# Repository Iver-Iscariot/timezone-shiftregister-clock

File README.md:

# Timezone clock
Expandable, dynamic system for showing the time in different timezones.

Originally designed for use in Omega Verksted, as several members exchanged to different timezones.

The modules are chained together with one MCU at the end. The timezone for each module is set using the dip switch, and read to the MCU by shift registers. The corresponding numbers for 7-seg displays are then sent out on further registers. The dip-switch also instructs weather its the last in the chain, and if its supposed to show the minutes or the hours of the zone. The clock is design to be installed in two rows, one for hours and one for minutes

## Time zone DIP switch table
coming

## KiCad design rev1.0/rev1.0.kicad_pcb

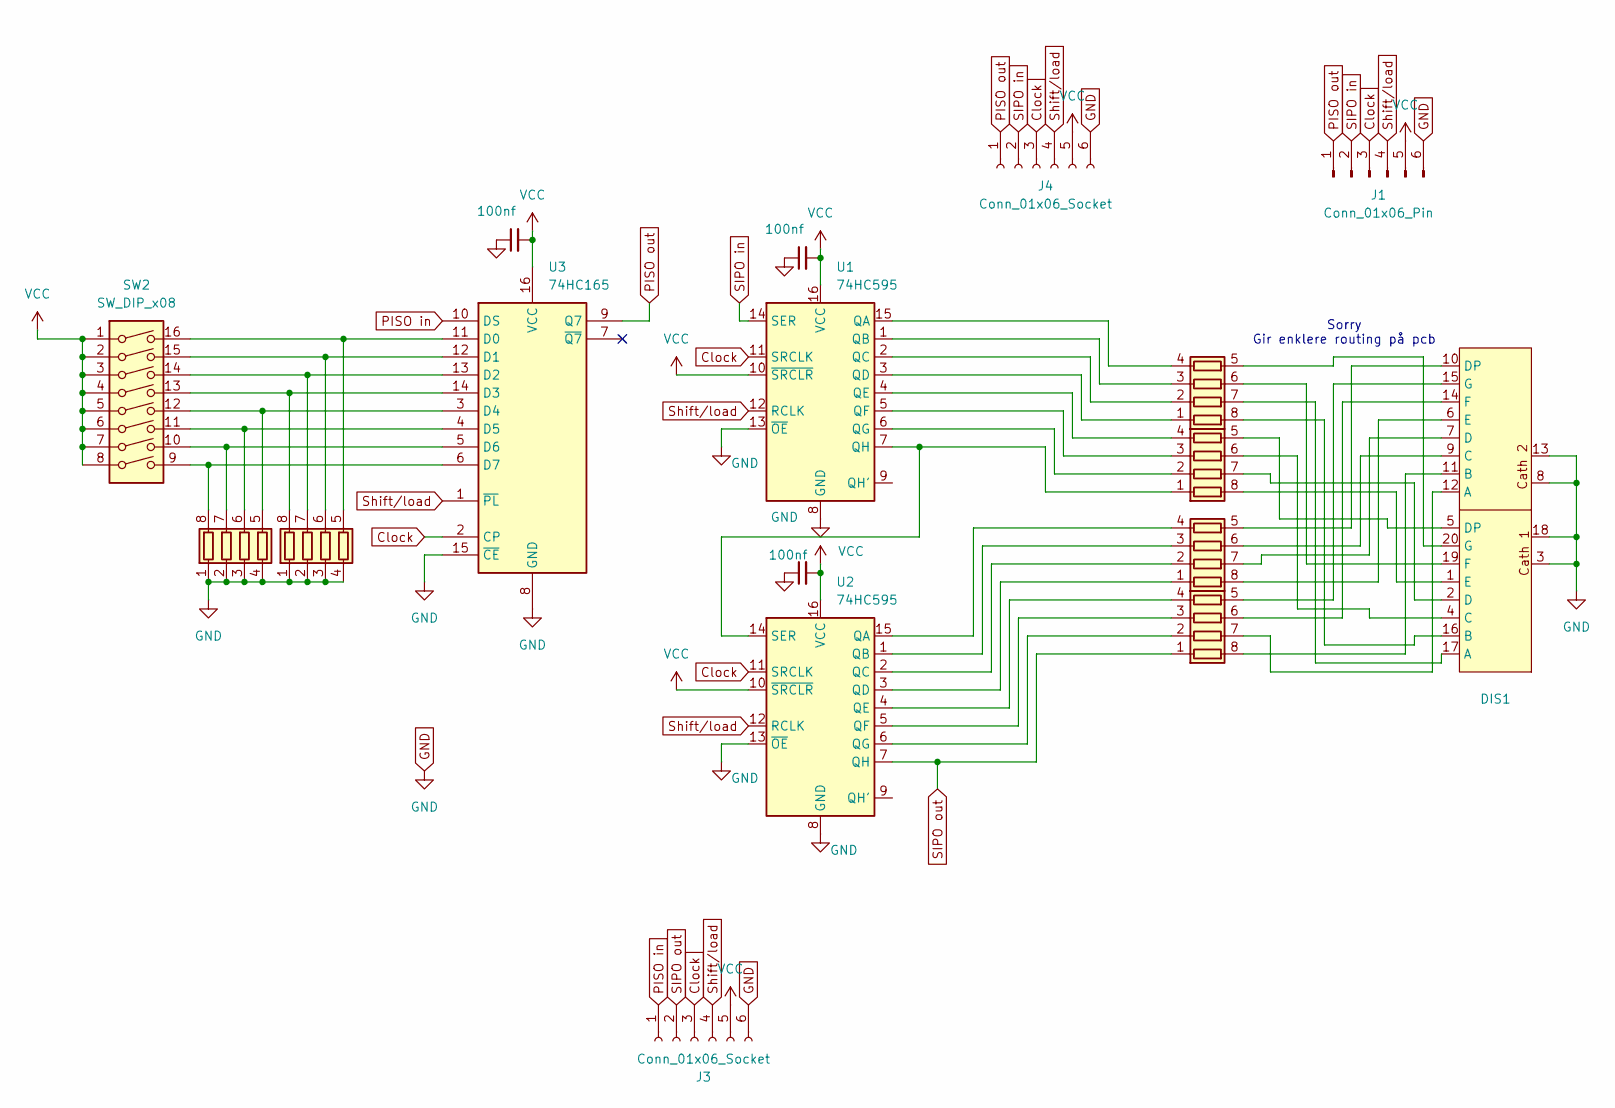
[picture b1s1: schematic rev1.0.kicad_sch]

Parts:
C1, C2, C3: 100nf; C_0603_1608Metric
DIS1: double digit 7 seg
J1: Conn_01x06_Pin; PinHeader_1x06_P2.54mm_Horizontal
J3, J4: Conn_01x06_Socket; flatcable conn 6
RN1, RN2, RN3, RN4, RN5, RN6: R_Pack04; R_Array_Concave_4x0603
SW2: SW_DIP_x08; SOIC-16_3.9x9.9mm_P1.27mm
U1, U2: 74HC595; SOIC-16_3.9x9.9mm_P1.27mm
U3: 74HC165; SOIC-16_3.9x9.9mm_P1.27mm

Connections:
Clock: J1.3, J3.3, J4.3, U1.11 (SRCLK), U2.11 (SRCLK), U3.2 (CP)
GND: C1.1, C2.1, C3.1, DIS1.3, DIS1.8, DIS1.13, DIS1.18, J1.6, J3.6, J4.6, RN1.1 (R1.1), RN1.2 (R2.1), RN1.3 (R3.1), RN1.4 (R4.1), RN2.1 (R1.1), RN2.2 (R2.1), RN2.3 (R3.1), RN2.4 (R4.1), U1.8 (GND), U1.13 (~OE), U2.8 (GND), U2.13 (~OE), U3.8 (GND), U3.15 (~CE)
unnamed: RN1.8 (R1.2), SW2.9, U3.6 (D7)
unnamed: RN1.7 (R2.2), SW2.10, U3.5 (D6)
unnamed: RN1.6 (R3.2), SW2.11, U3.4 (D5)
unnamed: RN1.5 (R4.2), SW2.12, U3.3 (D4)
unnamed: RN2.8 (R1.2), SW2.13, U3.14 (D3)
unnamed: RN2.7 (R2.2), SW2.14, U3.13 (D2)
unnamed: RN2.6 (R3.2), SW2.15, U3.12 (D1)
unnamed: RN2.5 (R4.2), SW2.16, U3.11 (D0)
unnamed: RN3.1 (R1.1), U1.3 (QD)
unnamed: DIS1.16 (B), RN3.8 (R1.2)
unnamed: RN3.2 (R2.1), U1.2 (QC)
unnamed: DIS1.17 (A), RN3.7 (R2.2)
unnamed: RN3.3 (R3.1), U1.1 (QB)
unnamed: DIS1.19 (F), RN3.6 (R3.2)
unnamed: RN3.4 (R4.1), U1.15 (QA)
unnamed: DIS1.20 (G), RN3.5 (R4.2)
unnamed: DIS1.11 (B), RN4.8 (R1.2)
unnamed: RN4.2 (R2.1), U2.6 (QG)
unnamed: DIS1.12 (A), RN4.7 (R2.2)
unnamed: RN4.3 (R3.1), U2.5 (QF)
unnamed: DIS1.14 (F), RN4.6 (R3.2)
unnamed: RN4.4 (R4.1), U2.4 (QE)
unnamed: DIS1.15 (G), RN4.5 (R4.2)
unnamed: RN5.1 (R1.1), U2.3 (QD)
unnamed: DIS1.6 (E), RN5.8 (R1.2)
unnamed: RN5.2 (R2.1), U2.2 (QC)
unnamed: DIS1.7 (D), RN5.7 (R2.2)
unnamed: RN5.3 (R3.1), U2.1 (QB)
unnamed: DIS1.9 (C), RN5.6 (R3.2)
unnamed: RN5.4 (R4.1), U2.15 (QA)
unnamed: DIS1.10 (DP), RN5.5 (R4.2)
unnamed: RN6.1 (R1.1), U1.7 (QH), U2.14 (SER)
unnamed: DIS1.1 (E), RN6.8 (R1.2)
unnamed: RN6.2 (R2.1), U1.6 (QG)
unnamed: DIS1.2 (D), RN6.7 (R2.2)
unnamed: RN6.3 (R3.1), U1.5 (QF)
unnamed: DIS1.4 (C), RN6.6 (R3.2)
unnamed: RN6.4 (R4.1), U1.4 (QE)
unnamed: DIS1.5 (DP), RN6.5 (R4.2)
PISO in: J3.1, U3.10 (DS)
PISO out: J1.1, J4.1, U3.9 (Q7)
SIPO in: J1.2, J4.2, U1.14 (SER)
SIPO out: J3.2, RN4.1 (R1.1), U2.7 (QH)
Shift/load: J1.4, J3.4, J4.4, U1.12 (RCLK), U2.12 (RCLK), U3.1 (~PL)
VCC: C1.2, C2.2, C3.2, J1.5, J3.5, J4.5, SW2.1, SW2.2, SW2.3, SW2.4, SW2.5, SW2.6, SW2.7, SW2.8, U1.10 (~SRCLR), U1.16 (VCC), U2.10 (~SRCLR), U2.16 (VCC), U3.16 (VCC)

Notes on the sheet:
Sorry Gir enklere routing på pcb

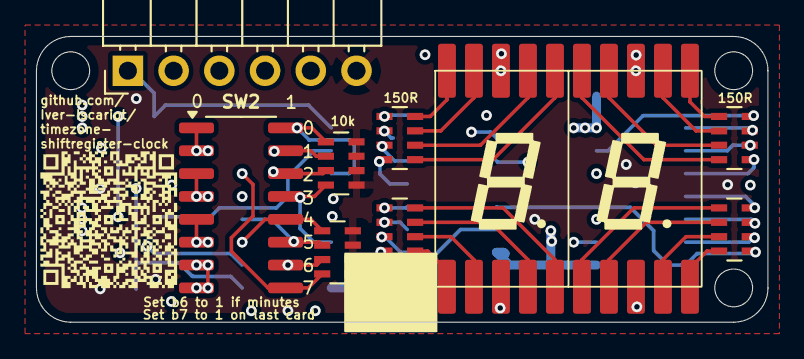
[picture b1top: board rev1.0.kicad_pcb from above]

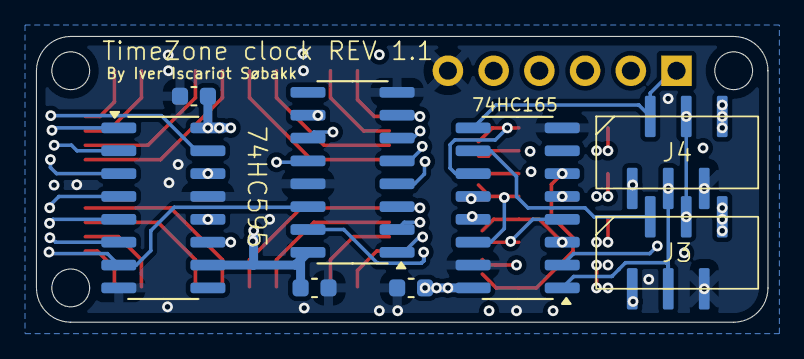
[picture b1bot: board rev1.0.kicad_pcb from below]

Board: 4 copper layers, 40.6 x 15.9 mm, 17 parts (8 on the bottom side), 47 nets.

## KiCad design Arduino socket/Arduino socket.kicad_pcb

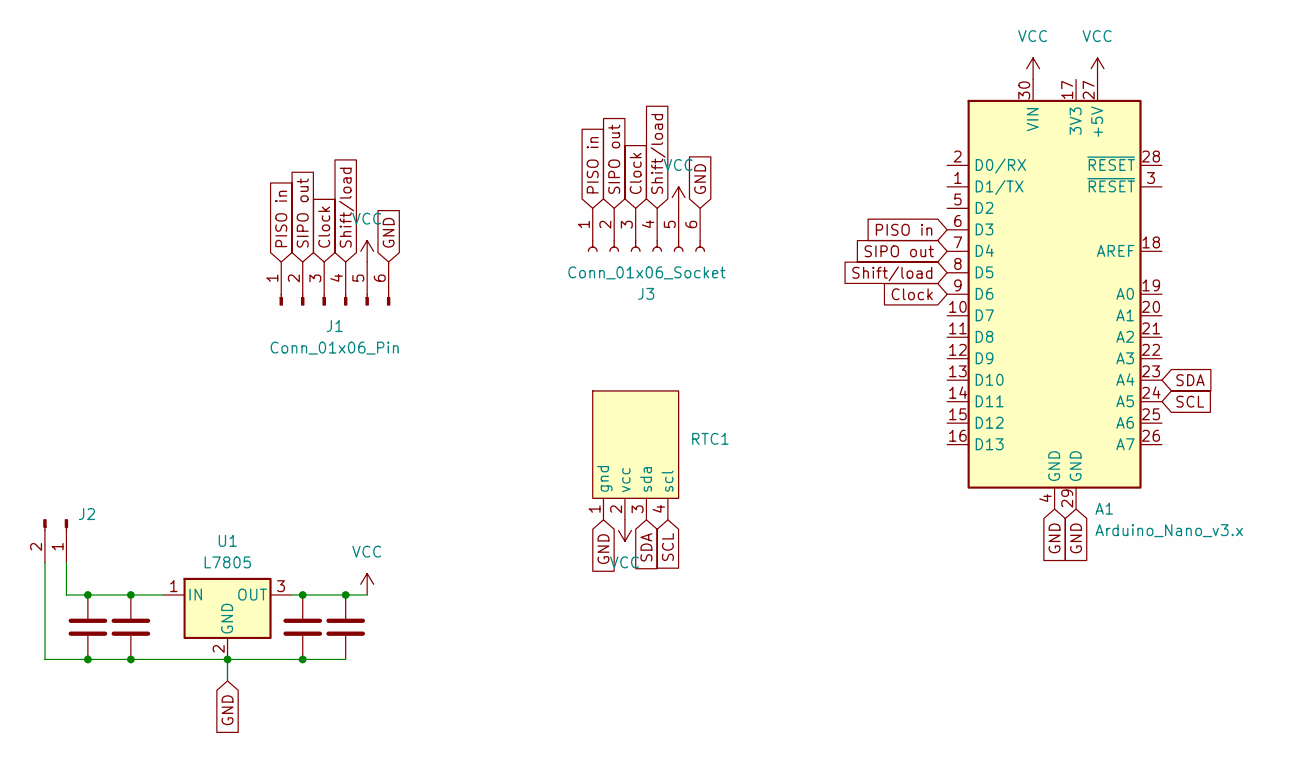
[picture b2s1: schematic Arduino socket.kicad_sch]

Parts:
A1: Arduino_Nano_v3.x; Arduino_Nano
C1, C2, C3, C4: C; C_0805_2012Metric_Pad1.18x1.45mm_HandSolder
J1: Conn_01x06_Pin; PinHeader_1x06_P2.54mm_Horizontal
J2: Conn_01x02_Pin; PinHeader_1x02_P2.54mm_Vertical
J3: Conn_01x06_Socket; flatcable conn 6
RTC1: DS3231 RTC module
U1: L7805; TO-220-3_Horizontal_TabDown

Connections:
Clock: A1.9 (D6), J1.3, J3.3
GND: A1.4 (GND), A1.29 (GND), C1.2, C2.2, C3.2, C4.2, J1.6, J2.2, J3.6, RTC1.1 (gnd), U1.2 (GND)
unnamed: C1.1, C2.1, J2.1, U1.1 (IN)
PISO in: A1.6 (D3), J1.1, J3.1
SCL: A1.24 (A5), RTC1.4 (scl)
SDA: A1.23 (A4), RTC1.3 (sda)
SIPO out: A1.7 (D4), J1.2, J3.2
Shift/load: A1.8 (D5), J1.4, J3.4
VCC: A1.27 (+5V), A1.30 (VIN), C3.1, C4.1, J1.5, J3.5, RTC1.2 (vcc), U1.3 (OUT)

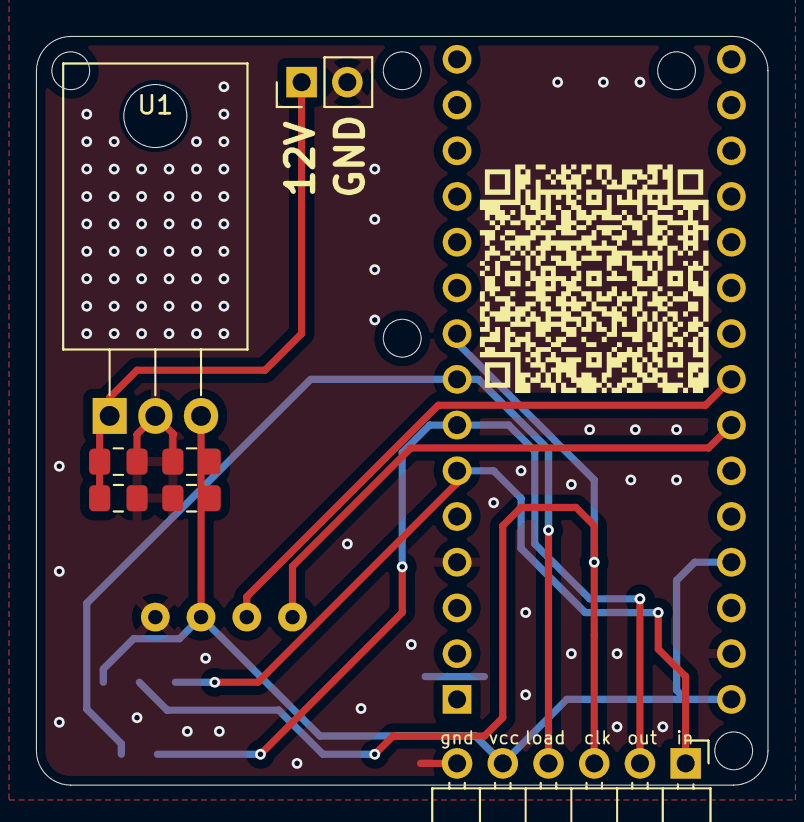
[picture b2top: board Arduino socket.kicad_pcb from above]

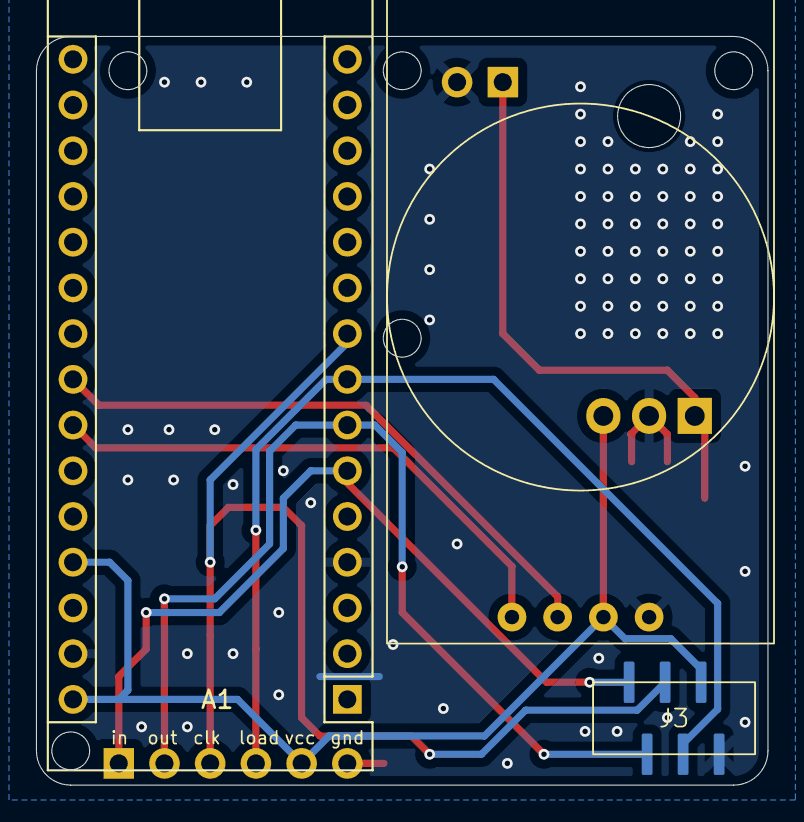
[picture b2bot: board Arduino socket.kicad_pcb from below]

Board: 2 copper layers, 40.6 x 41.6 mm, 10 parts (2 on the bottom side), 9 nets.

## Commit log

2025-06-17 Started work on circuit
2025-06-18 More wokr. Må bare koble sammen headers og registere
2025-06-18 Added last connections in schematic. just missing routing
2025-06-18 oop, forgot the PCB changes
2025-06-20 Gikk over til 4-lags for å få det mye mindre.
    Byttet også over til en full 8pin DIP-swith, og mindre pakke en jeg hadde først
2025-06-21 Completed pcb for module, and started an arduino socket w/ interconnect
2025-08-21 Started coding.
    Reading and writing to registers implemented.
    The circuit is now on rev 1.1, but there were some mistakes on this one to, hehe.
    The dip-switch is NOT the same size as a 16p soic, a little wider (bodgedd by bending pins under on one side (the one thats just all vcc anyways, as it can be bridged if you're struggeling with the j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
    The socket also has some mechanical solder points on the ends, that wasnt on my footprint. They are also thinner and longer than thought. The mechanical solder on one side could short some pins on th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
2025-08-26 Added a little more time stuff
